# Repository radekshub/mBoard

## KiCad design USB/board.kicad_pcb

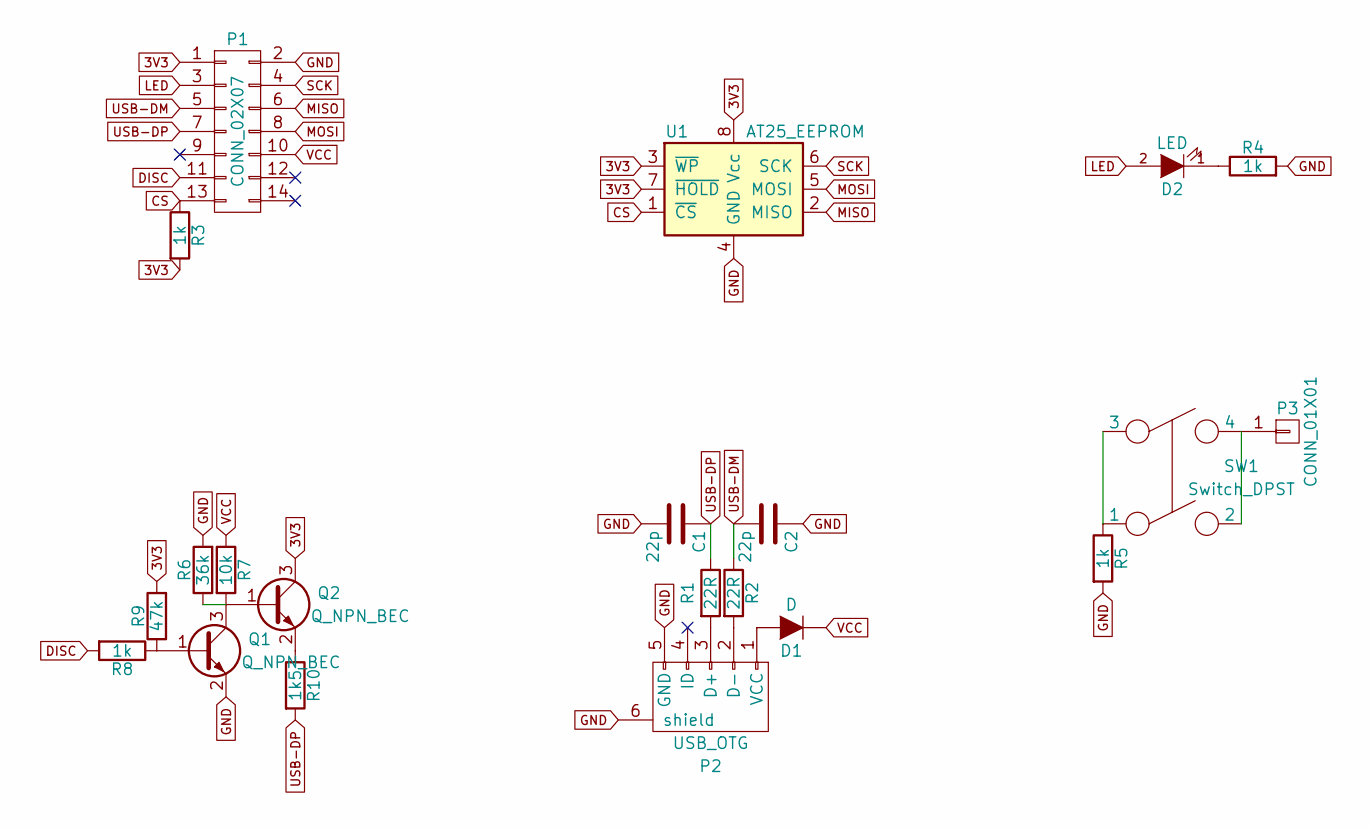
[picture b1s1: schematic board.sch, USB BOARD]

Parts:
C1, C2: 22p; C_0805
D1: D; SMA_Standard
D2: LED; LED_0805
P1: CONN_02X07; Pin_Header_Straight_2x07
P2: USB_OTG; USB_Micro-B
P3: CONN_01X01; Pin_Header_Straight_1x01
Q1, Q2: Q_NPN_BEC; SOT-23
R1, R2: 22R; R_0805
R3, R4, R5, R8: 1k; R_0805
R6: 36k; R_0805
R7: 10k; R_0805
R9: 47k; R_0805
R10: 1k5; R_0805
SW1: Switch_DPST; SW_TH_Tactile_Omron_B3F-10xx
U1: AT25_EEPROM; SOIC-8-N

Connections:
3V3: P1.1, Q2.3 (C), R3.2, R9.2, U1.3 (~WP), U1.7 (~HOLD), U1.8 (Vcc)
CS: P1.13, R3.1, U1.1 (~CS)
DISC: P1.11, R8.2
GND: C1.2, C2.1, P1.2, P2.5 (GND), P2.6 (shield), Q1.2 (E), R4.2, R5.2, R6.2, U1.4 (GND)
LED: D2.2 (A), P1.3
MISO: P1.6, U1.2 (MISO)
MOSI: P1.8, U1.5 (MOSI)
unnamed: D1.2 (A), P2.1 (VCC)
unnamed: D2.1 (K), R4.1
unnamed: P2.2 (D-), R2.2
unnamed: P2.3 (D+), R1.2
unnamed: P3.1, SW1.2, SW1.4
unnamed: Q1.1 (B), R8.1, R9.1
unnamed: Q1.3 (C), Q2.1 (B), R6.1, R7.2
unnamed: Q2.2 (E), R10.1
unnamed: R5.1, SW1.1, SW1.3
SCK: P1.4, U1.6 (SCK)
USB-DM: C2.2, P1.5, R2.1
USB-DP: C1.1, P1.7, R1.1, R10.2
VCC: D1.1 (K), P1.10, R7.1

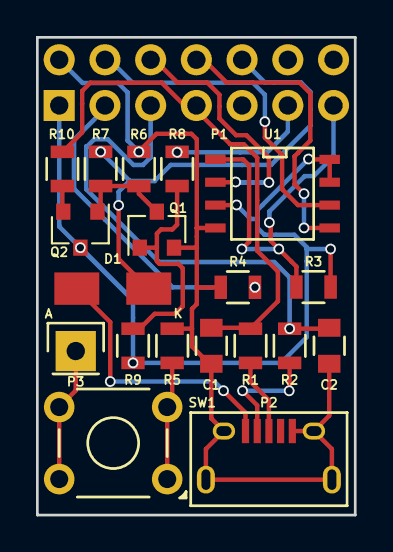
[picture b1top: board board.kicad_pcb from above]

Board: 2 copper layers, 17.7 x 26.5 mm, 21 parts (1 on the bottom side), 20 nets.

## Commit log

2019-10-27 USB README
2019-10-27 USB board was added.

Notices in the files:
USB/board.kicad_pcb:
Copyright © 2016
